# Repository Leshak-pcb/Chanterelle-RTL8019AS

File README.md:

# Chanterelle-RTL8019AS
Warning! Not tested yet, may contain critical errors. Realtek RTL8019AS 8-bit ISA ethernet card.
upd: fixed rtl8019as footprint - sadly, KiCAD pqfp-100 footprint was smaller than needed.

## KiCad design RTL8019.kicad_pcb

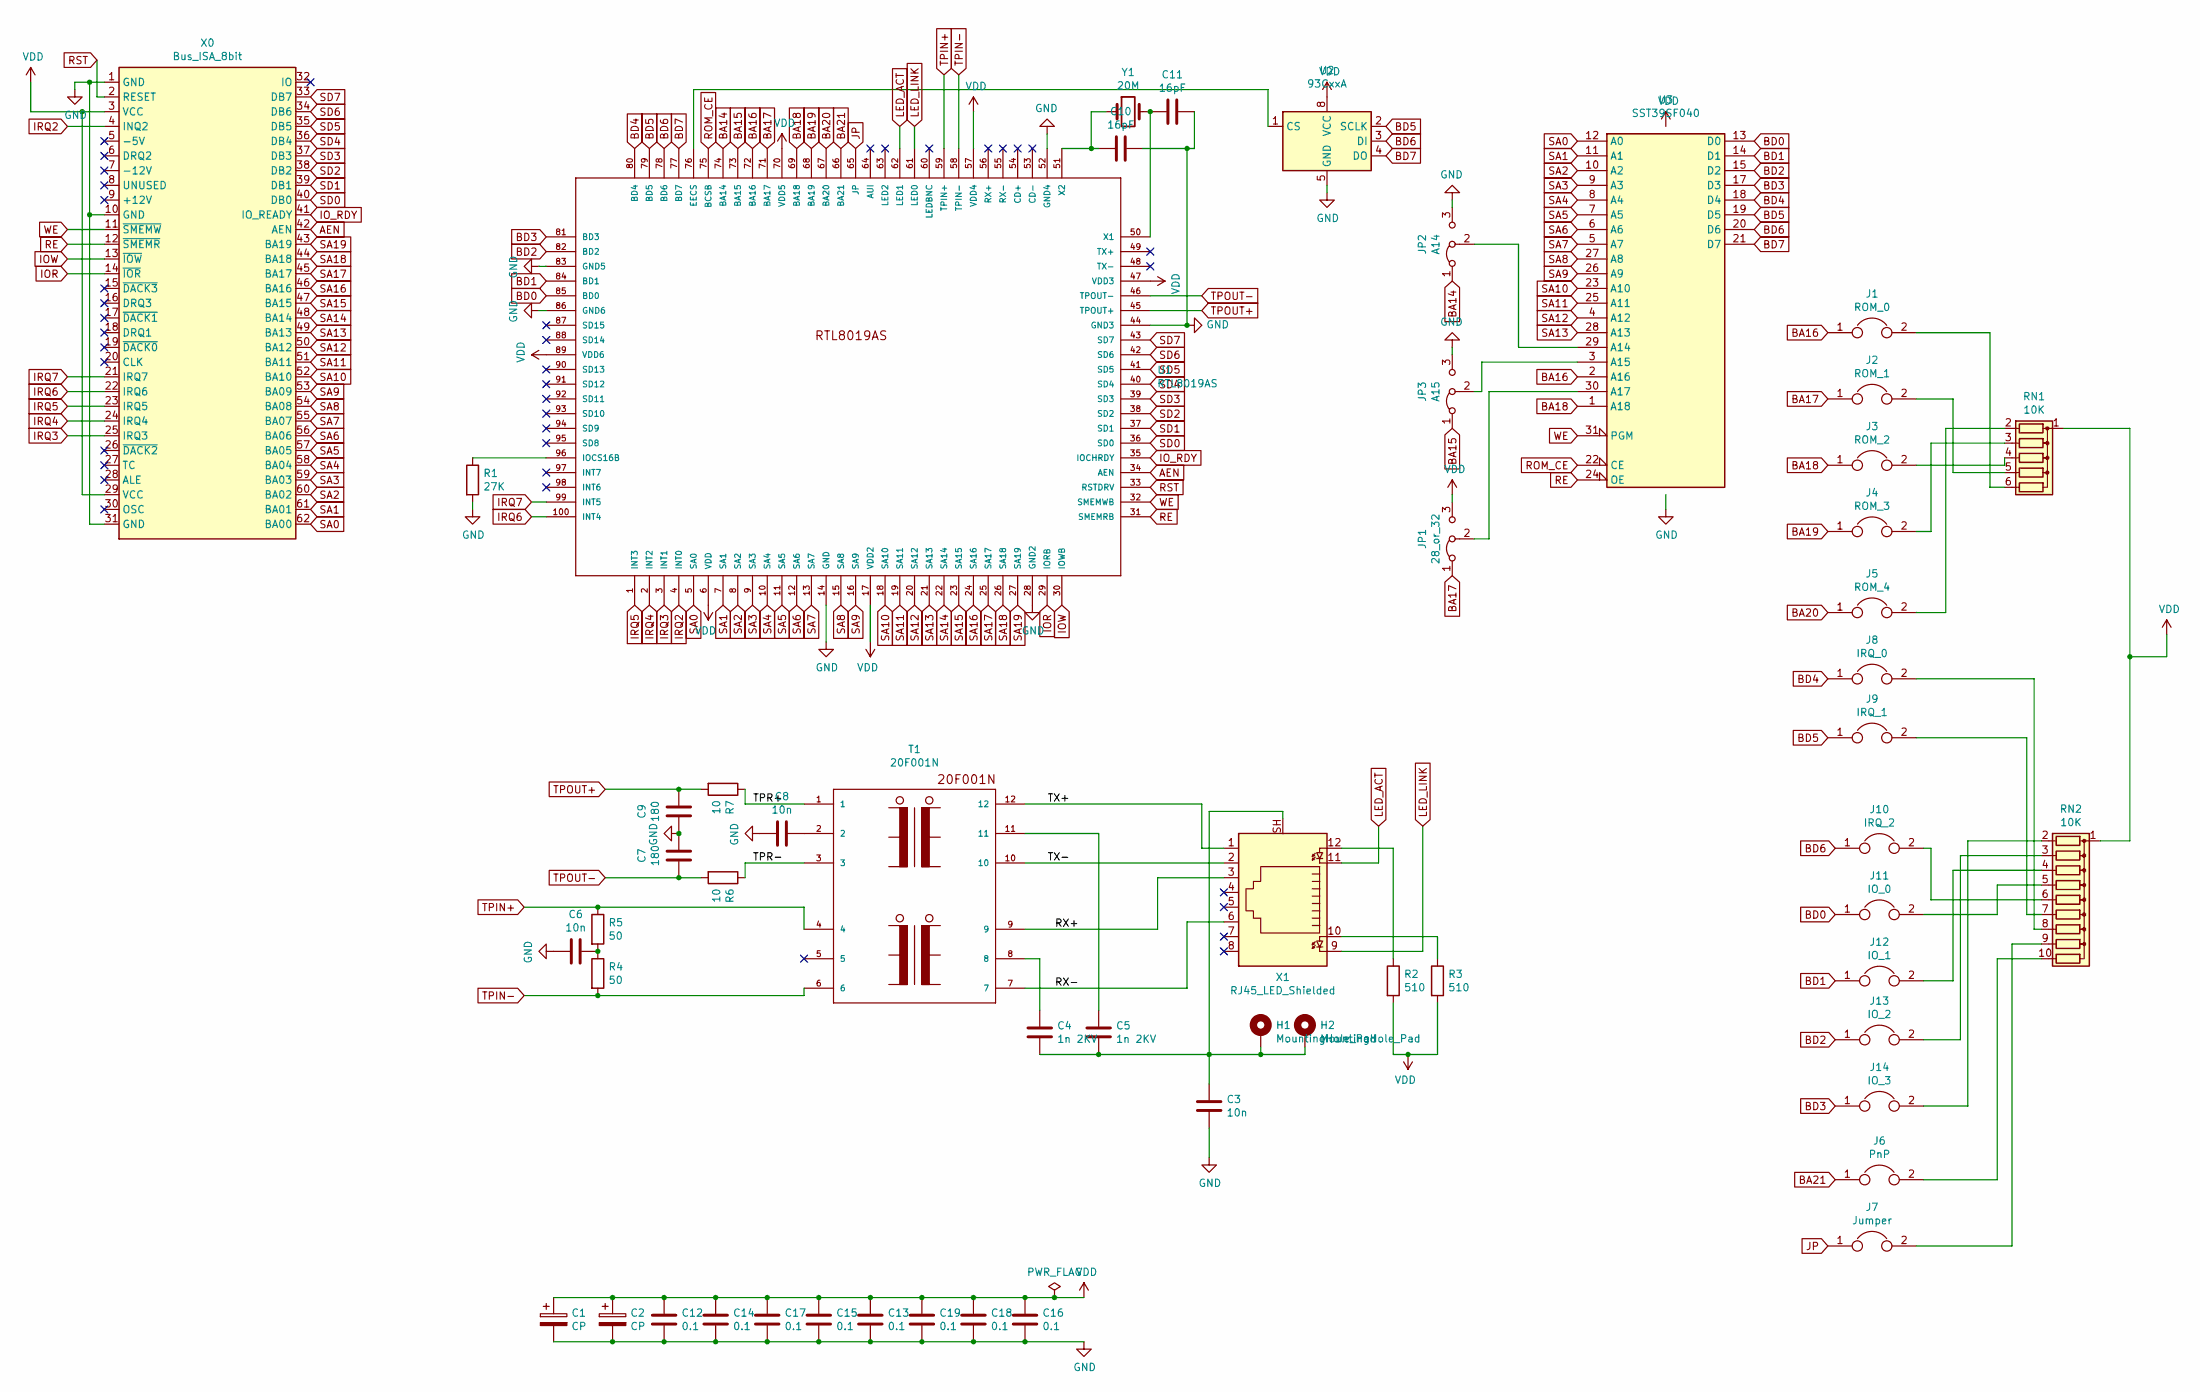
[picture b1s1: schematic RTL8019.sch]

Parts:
C1, C2: CP; CP_Radial_D5.0mm_P2.00mm
C3: 10n; C_1206_3216Metric_Pad1.42x1.75mm_HandSolder
C4, C5: 1n 2KV; C_Disc_D9.0mm_W5.0mm_P7.50mm
C6, C8: 10n; C_0805_2012Metric
C7, C9: 180; C_0805_2012Metric
C10, C11: 16pF; C_0805_2012Metric
C12, C13, C14, C15, C16, C17, C18, C19: 0.1; C_0805_2012Metric
H1, H2: MountingHole_Pad; MountingHole_3.2mm_M3_DIN965_Pad
J1: ROM_0; PinHeader_1x02_P2.54mm_Vertical
J2: ROM_1; PinHeader_1x02_P2.54mm_Vertical
J3: ROM_2; PinHeader_1x02_P2.54mm_Vertical
J4: ROM_3; PinHeader_1x02_P2.54mm_Vertical
J5: ROM_4; PinHeader_1x02_P2.54mm_Vertical
J6: PnP; PinHeader_1x02_P2.54mm_Vertical
J7: Jumper; PinHeader_1x02_P2.54mm_Vertical
J8: IRQ_0; PinHeader_1x02_P2.54mm_Vertical
J9: IRQ_1; PinHeader_1x02_P2.54mm_Vertical
J10: IRQ_2; PinHeader_1x02_P2.54mm_Vertical
J11: IO_0; PinHeader_1x02_P2.54mm_Vertical
J12: IO_1; PinHeader_1x02_P2.54mm_Vertical
J13: IO_2; PinHeader_1x02_P2.54mm_Vertical
J14: IO_3; PinHeader_1x02_P2.54mm_Vertical
JP1: 28_or_32; PinHeader_1x03_P2.54mm_Vertical
JP2: A14; PinHeader_1x03_P2.54mm_Vertical
JP3: A15; PinHeader_1x03_P2.54mm_Vertical
R1: 27K; R_0805_2012Metric
R2, R3: 510; R_0805_2012Metric
R4, R5: 50; R_0805_2012Metric
R6, R7: 10; R_0805_2012Metric
RN1: 10K; R_Array_SIP6
RN2: 10K; R_Array_SIP10
T1: 20F001N; 20f001ng
U1: RTL8019AS; 8019as
U2: 93CxxA; SOIC-8_3.9x4.9mm_P1.27mm
U3: SST39SF040; DIP-32_W15.24mm_Socket
X0: Bus_ISA_8bit; Conn_Edge_PCB_ISA8
X1: RJ45_LED_Shielded; RJ45_Amphenol_RJHSE538X
Y1: 20M; Crystal_HC49-U_Vertical

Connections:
/RX+: T1.9, X1.3
/RX-: T1.7, X1.6
/TPR+: R7.1, T1.1
/TPR-: R6.1, T1.3
/TX+: T1.12, X1.1
/TX-: T1.10, X1.2
AEN: U1.34 (AEN), X0.42 (AEN)
BA14: JP2.1 (A), U1.74 (BA14)
BA15: JP3.1 (A), U1.73 (BA15)
BA16: J1.1, U1.72 (BA16), U3.2 (A16)
BA17: J2.1, JP1.1 (A), U1.71 (BA17)
BA18: J3.1, U1.69 (BA18), U3.1 (A18)
BA19: J4.1, U1.68 (BA19)
BA20: J5.1, U1.67 (BA20)
BA21: J6.1, U1.66 (BA21)
BD0: J11.1, U1.85 (BD0), U3.13 (D0)
BD1: J12.1, U1.84 (BD1), U3.14 (D1)
BD2: J13.1, U1.82 (BD2), U3.15 (D2)
BD3: J14.1, U1.81 (BD3), U3.17 (D3)
BD4: J8.1, U1.80 (BD4), U3.18 (D4)
BD5: J9.1, U1.79 (BD5), U2.2 (SCLK), U3.19 (D5)
BD6: J10.1, U1.78 (BD6), U2.3 (DI), U3.20 (D6)
BD7: U1.77 (BD7), U2.4 (DO), U3.21 (D7)
GND: C1.2, C2.2, C3.1, C6.2, C7.1, C8.2, C9.2, C10.1, C11.2, C12.2, C13.2, C14.2, C15.2, C16.2, C17.2, C18.2, C19.2, JP2.3 (B), JP3.3 (B), R1.2, U1.14 (GND), U1.28 (GND2), U1.44 (GND3), U1.52 (GND4), U1.83 (GND5), U1.86 (GND6), U2.5 (GND), U3.16 (GND), X0.1 (GND), X0.10 (GND), X0.31 (GND)
IOR: U1.29 (IORB), X0.14 (~IOR)
IOW: U1.30 (IOWB), X0.13 (~IOW)
IO_RDY: U1.35 (IOCHRDY), X0.41 (IO_READY)
IRQ2: U1.4 (INT0), X0.4 (INQ2)
IRQ3: U1.3 (INT1), X0.25 (IRQ3)
IRQ4: U1.2 (INT2), X0.24 (IRQ4)
IRQ5: U1.1 (INT3), X0.23 (IRQ5)
IRQ6: U1.100 (INT4), X0.22 (IRQ6)
IRQ7: U1.99 (INT5), X0.21 (IRQ7)
JP: J7.1, U1.65 (JP)
LED_ACT: U1.62 (LED1), X1.11
LED_LINK: U1.61 (LED0), X1.9
unnamed: C3.2, C4.1, C5.1, H1.1, H2.1, X1.SH
unnamed: C4.2, T1.8
unnamed: C5.2, T1.11
unnamed: C6.1, R4.1, R5.2
unnamed: C8.1, T1.2
unnamed: C10.2, U1.51 (X2), Y1.1
unnamed: C11.1, U1.50 (X1), Y1.2
unnamed: J1.2, RN1.6 (R5)
unnamed: J2.2, RN1.5 (R4)
unnamed: J3.2, RN1.4 (R3)
unnamed: J4.2, RN1.3 (R2)
unnamed: J5.2, RN1.2 (R1)
unnamed: J6.2, RN2.10 (R9)
unnamed: J7.2, RN2.9 (R8)
unnamed: J8.2, RN2.8 (R7)
unnamed: J9.2, RN2.7 (R6)
unnamed: J10.2, RN2.6 (R5)
unnamed: J11.2, RN2.5 (R4)
unnamed: J12.2, RN2.4 (R3)
unnamed: J13.2, RN2.3 (R2)
unnamed: J14.2, RN2.2 (R1)
unnamed: JP1.2 (C), U3.30 (A17)
unnamed: JP2.2 (C), U3.29 (A14)
unnamed: JP3.2 (C), U3.3 (A15)
unnamed: R1.1, U1.96 (IOCS16B)
unnamed: R2.1, X1.12
unnamed: R3.1, X1.10
unnamed: U1.76 (EECS), U2.1 (CS)
RE: U1.31 (SMEMRB), U3.24 (OE), X0.12 (~SMEMR)
ROM_CE: U1.75 (BCSB), U3.22 (CE)
RST: U1.33 (RSTDRV), X0.2 (RESET)
SA0: U1.5 (SA0), U3.12 (A0), X0.62 (BA00)
SA1: U1.7 (SA1), U3.11 (A1), X0.61 (BA01)
SA2: U1.8 (SA2), U3.10 (A2), X0.60 (BA02)
SA3: U1.9 (SA3), U3.9 (A3), X0.59 (BA03)
SA4: U1.10 (SA4), U3.8 (A4), X0.58 (BA04)
SA5: U1.11 (SA5), U3.7 (A5), X0.57 (BA05)
SA6: U1.12 (SA6), U3.6 (A6), X0.56 (BA06)
SA7: U1.13 (SA7), U3.5 (A7), X0.55 (BA07)
SA8: U1.15 (SA8), U3.27 (A8), X0.54 (BA08)
SA9: U1.16 (SA9), U3.26 (A9), X0.53 (BA09)
SA10: U1.18 (SA10), U3.23 (A10), X0.52 (BA10)
SA11: U1.19 (SA11), U3.25 (A11), X0.51 (BA11)
SA12: U1.20 (SA12), U3.4 (A12), X0.50 (BA12)
SA13: U1.21 (SA13), U3.28 (A13), X0.49 (BA13)
SA14: U1.22 (SA14), X0.48 (BA14)
SA15: U1.23 (SA15), X0.47 (BA15)
SA16: U1.24 (SA16), X0.46 (BA16)
SA17: U1.25 (SA17), X0.45 (BA17)
SA18: U1.26 (SA18), X0.44 (BA18)
SA19: U1.27 (SA19), X0.43 (BA19)
SD0: U1.36 (SD0), X0.40 (DB0)
SD1: U1.37 (SD1), X0.39 (DB1)
SD2: U1.38 (SD2), X0.38 (DB2)
SD3: U1.39 (SD3), X0.37 (DB3)
SD4: U1.40 (SD4), X0.36 (DB4)
SD5: U1.41 (SD5), X0.35 (DB5)
SD6: U1.42 (SD6), X0.34 (DB6)
SD7: U1.43 (SD7), X0.33 (DB7)
TPIN+: R5.1, T1.4, U1.59 (TPIN+)
TPIN-: R4.2, T1.6, U1.58 (TPIN-)
TPOUT+: C9.1, R7.2, U1.45 (TPOUT+)
TPOUT-: C7.2, R6.2, U1.46 (TPOUT-)
VCC: C1.1, C2.1, C12.1, C13.1, C14.1, C15.1, C16.1, C17.1, C18.1, C19.1, JP1.3 (B), R2.2, R3.2, RN1.1 (common), RN2.1 (common), U1.6 (VDD), U1.17 (VDD2), U1.47 (VDD3), U1.57 (VDD4), U1.70 (VDD5), U1.89 (VDD6), U2.8 (VCC), U3.32 (VCC), X0.3 (VCC), X0.29 (VCC)
WE: U1.32 (SMEMWB), U3.31 (PGM), X0.11 (~SMEMW)

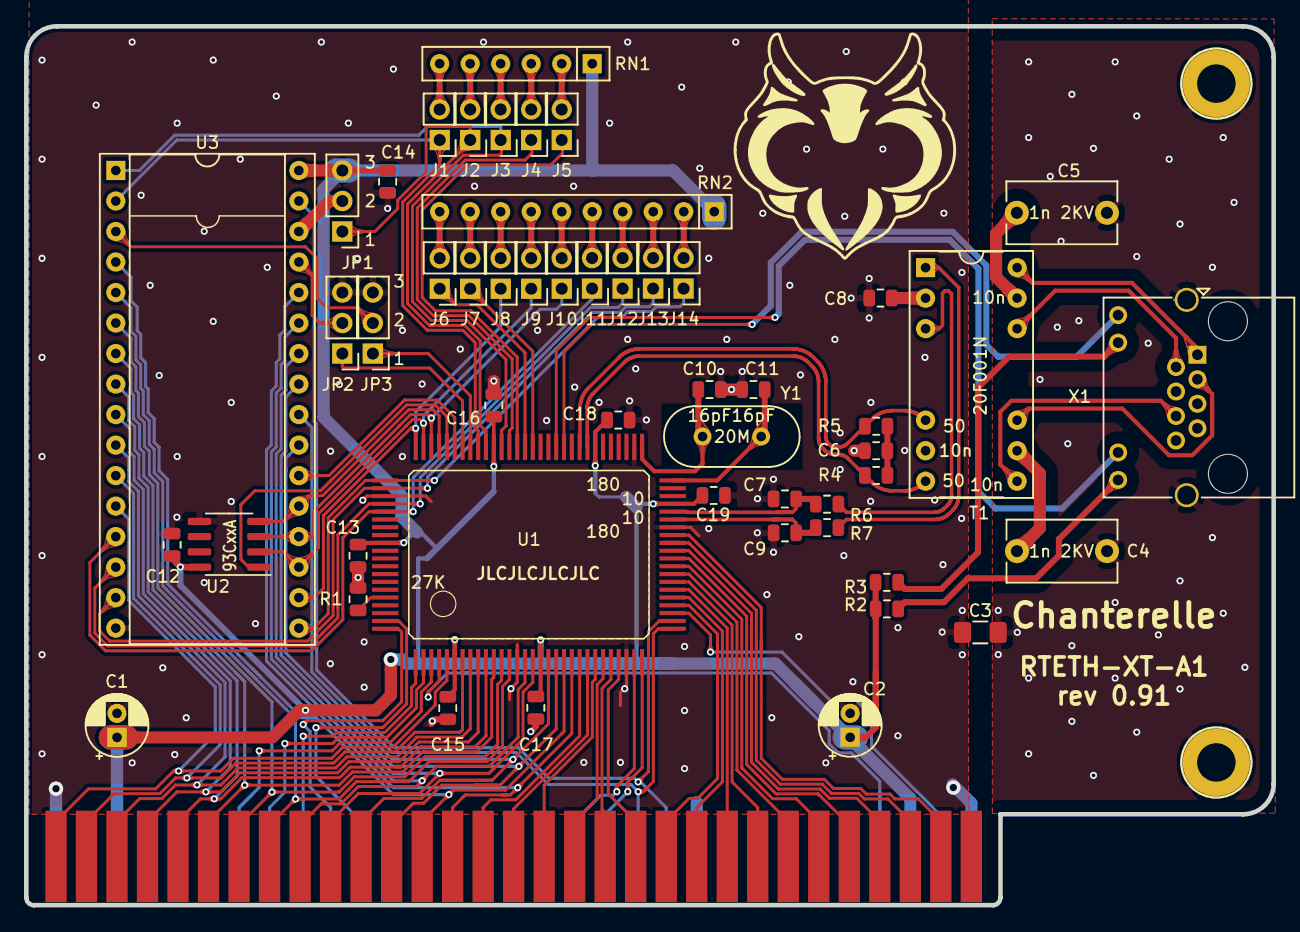
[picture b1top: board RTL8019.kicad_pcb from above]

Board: 2 copper layers, 103.8 x 73.2 mm, 54 parts (0 on the bottom side), 101 nets.

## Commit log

2020-07-05 Add files via upload
    v0.9 PCB & schematics
2020-07-07 Add files via upload
    Added info string to pcb
2021-08-20 Add files via upload
    Fixed - incorrect rtl8019as footprint
